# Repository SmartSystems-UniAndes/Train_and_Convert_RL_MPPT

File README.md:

# Train_RL_MPPT
This repository was created for training reinforcement learning agents applied to the problem of maximum power point tracking. It includes the procedure used in order to convert the model to a tensorflowlite agent.  It also includes the schematics of the Buck Converter used to carry out the training process.

To continue deploying the model into the raspberry pi, the next step would be to follow the steps presented in the Github repository presented [here](https://github.com/SmartSystems-UniAndes/Reinforcement_Learning_MPPT_RaspberryPi_Deploy).

## Train_Agent Folder

The Train_Agent folder contains matlab and simulink files that are meant to be used with Matlab2022b. EnvDQN.mlx is a file in which the training parameters are set and the training process can be carried out there. SIM300kW_3paneles.slx is a simulink file that contains the environment used to train the RL model. VariablesBuck_paneles.mlx is a file that contains values for the capacitances and inductances used in the environment. It needs to be run before training the agent and it is excecuted at EnvDQN.mlx. localResetFcn_3paneles.m is a matlab file that resets the environment for each new episode generated. createDQNNetworks.m is the file in which the neural network used to train the DQN agent can be modified. At last, PandOAlgorithm.slx is a file that contains an environment where the Perturb and Observe algorithm can be tested.

## Convert_Agent_To_TFlite Folder
The Convert_Agent_To_TFlite folder contains a matlab script, called convert_script_onnx.m, that converts the agent created into a onnx file. The convert_onnx_to_tflite.ipynb file is intended to be used in google colab. This file allows the user to convert their onnx file to the tensorflow lite framework. The policy.onnx file created must be uploaded to colab to create the tflite model which can be downloaded once created.

## EAGLE_PCB_FILES/Buck300W_with_diode Folder
This folder contains the schematic and layout used to create the 300W synchronous Buck converter to test the models created in real experimental scenarios. It is possible to make it a synchronous  or non-synchronous if a MOSFET or a Diode is added to the low side of the converter. ADD JUST ONE OF THE TWO AT THE LOW SIDE, THE DIODE OR THE MOSFET. If you are using a raspberry pi with this circuit, DO NOT SUPPLY the SD pin of the IR2104 Driver (pin 3) with the 5V of the raspberry PI, this led to undesearable operations in our experiments. Furthermore, remember to add a heat sink to the high power MOSFETs. A diagram that depicts some of the elements of the synchronous buck converter in an schematic format can be seen next:

## Licenses
| Type | License |
| :------: | --- |
| Software    | [MIT License](https://opensource.org/licenses/MIT)     |
| Hardware  | [CERN-OHL-P](https://ohwr.org/project/cernohl/wikis/Documents/CERN-OHL-version-2)        |
| Documentation  | [CC BY 4.0](https://creativecommons.org/licenses/by/4.0/)    |

### Software
The software is licensed under an [MIT License](https://opensource.org/licenses/MIT). A copy of the license has been included in the repository and can be found [here](https://github.com/jfgf11/Reinforcement_Learning_MPPT/blob/main/LICENSE-MIT.txt).

### Hardware
The hardware design files are licensed under a CERN Open Source Hardware license version 2 CERN-OHL-P. Details of the license can be found [here](https://ohwr.org/project/cernohl/wikis/Documents/CERN-OHL-version-2) and a copy of the license has been included [here](https://github.com/jfgf11/Reinforcement_Learning_MPPT_RaspberryPi_Deploy/blob/main/LICENSE-CERN-OHL-P.txt).

### Documentation

This work is licensed under a [Creative Commons Attribution 4.0 International License](https://creativecommons.org/licenses/by/4.0/).

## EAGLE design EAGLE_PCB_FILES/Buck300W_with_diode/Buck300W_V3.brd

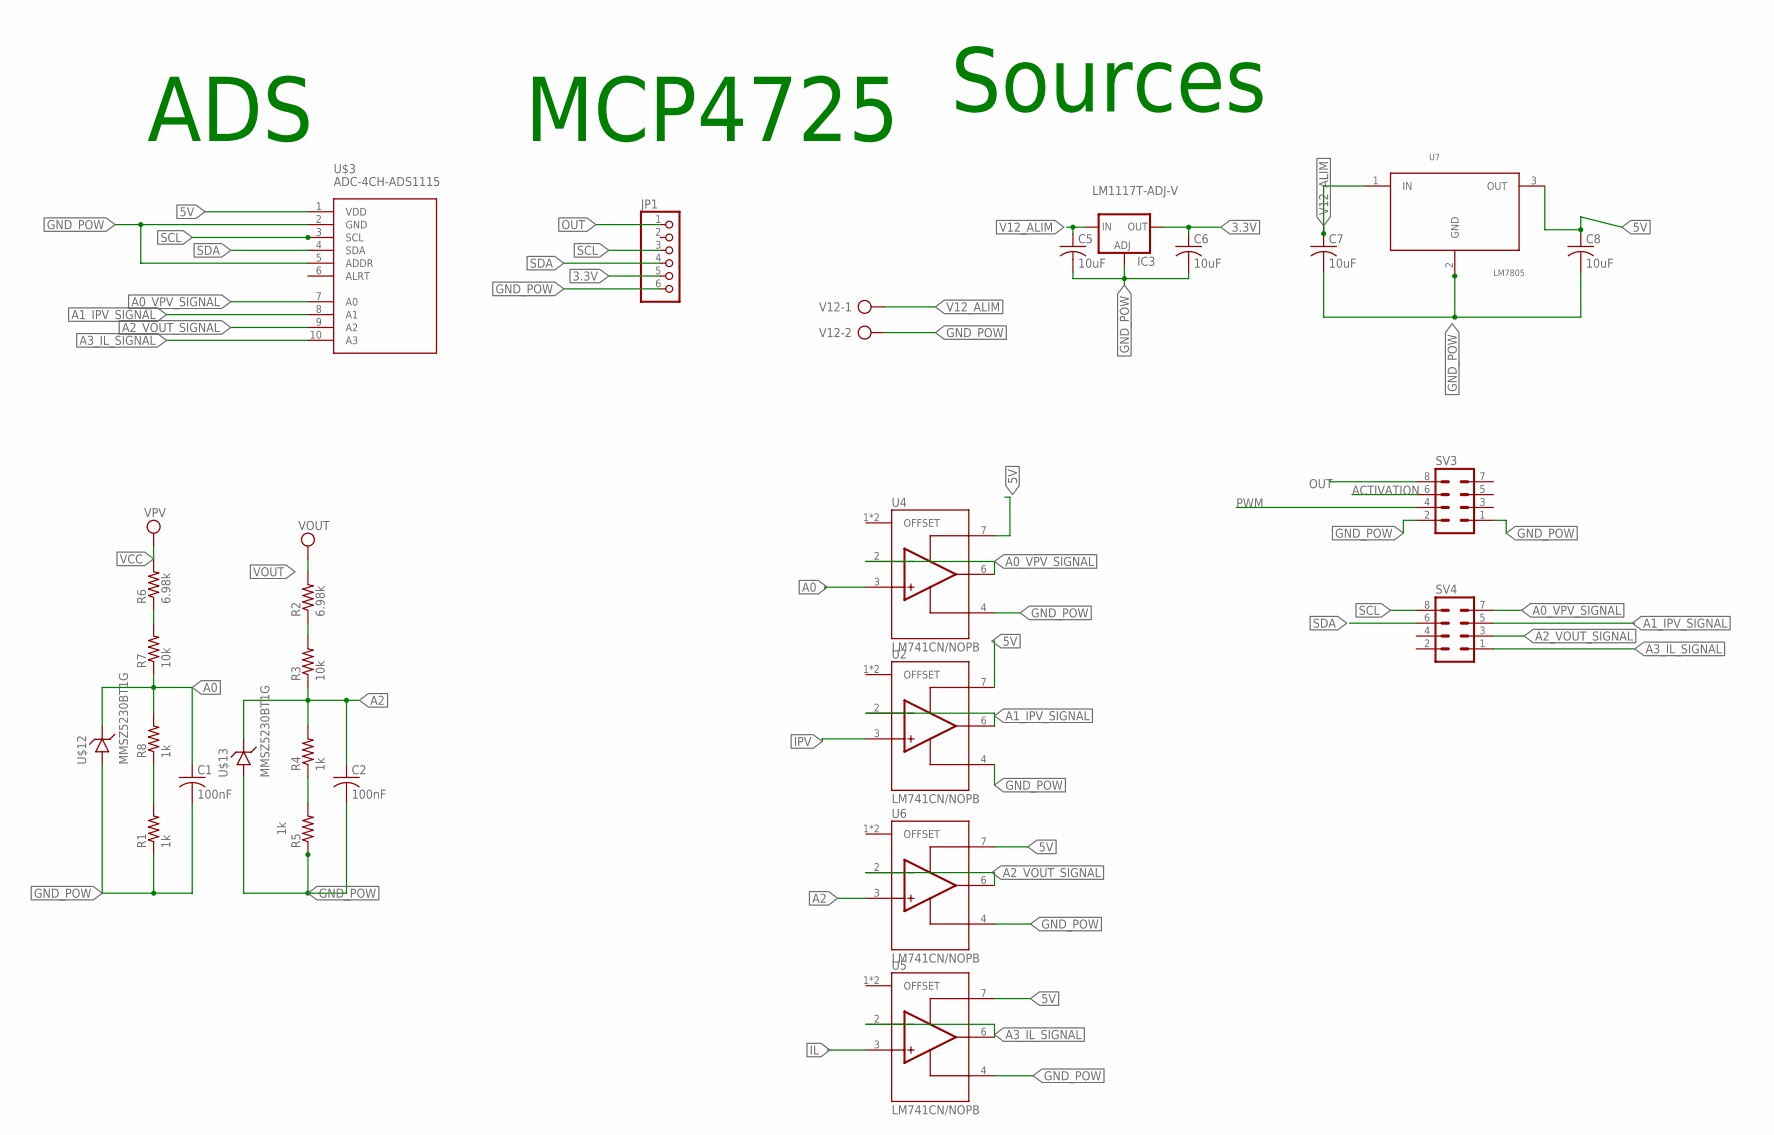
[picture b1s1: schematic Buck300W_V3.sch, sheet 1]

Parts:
C1, C2: 100nF; C0805
C5, C6, C7, C8: 10uF; C025-024X044
IC3: LM1117T-ADJ-V; TO220V
JP1: MICROBUILDER_HEADER-1X6; MICROBUILDER_1X06_OVAL
R1, R4, R5, R8: 1k; R0805
R2, R6: 6.98k; R0805
R3, R7: 10k; R0805
SV3, SV4: MA04-2
U2, U4, U5, U6: LM741CN/NOPB; DIP794W45P254L1016H508Q8
U7: LM7805; TO220
U$3: ADC-4CH-ADS1115
U$12, U$13: MMSZ5230BT1G; SOD3716X135N
V12: AK300/2

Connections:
3.3V: C6.1, IC3.2 (OUT), JP1.5
5V: C8.1, U2.7 (V+), U4.7 (V+), U5.7 (V+), U6.7 (V+), U7.3 (OUT), U$3.1 (VDD); also elsewhere on the board
A0: C1.1, R7.1, R8.2, U4.3 (NON-INV_INPUT), U$12.2 (ANODE)
A0_VPV_SIGNAL: SV4.7, U4.2 (INV_INPUT), U4.6 (OUTPUT), U$3.7 (A0)
A1_IPV_SIGNAL: SV4.5, U2.2 (INV_INPUT), U2.6 (OUTPUT), U$3.8 (A1)
A2: C2.1, R3.1, R4.2, U6.3 (NON-INV_INPUT), U$13.2 (ANODE)
A2_VOUT_SIGNAL: SV4.3, U6.2 (INV_INPUT), U6.6 (OUTPUT), U$3.9 (A2)
A3_IL_SIGNAL: SV4.1, U5.2 (INV_INPUT), U5.6 (OUTPUT), U$3.10 (A3)
ACTIVATION: SV3.6; also elsewhere on the board
GND_POW: C1.2, C2.2, C5.2, C6.2, C7.2, C8.2, IC3.1 (ADJ), JP1.6, R1.1, R5.1, SV3.1, SV3.2, U2.4 (V-), U4.4 (V-), U5.4 (V-), U6.4 (V-), U7.2 (GND), U$3.2 (GND), U$3.5 (ADDR), U$12.1 (CATHODE), U$13.1 (CATHODE), V12.2; also elsewhere on the board
IL: U5.3 (NON-INV_INPUT); also elsewhere on the board
IPV: U2.3 (NON-INV_INPUT); also elsewhere on the board
unnamed: R6.1, R7.2
unnamed: R2.1, R3.2
unnamed: R1.2, R8.1
unnamed: R4.1, R5.2
OUT: JP1.1, SV3.8; also elsewhere on the board
PWM: SV3.4; also elsewhere on the board
SCL: JP1.3, SV4.8, U$3.3 (SCL)
SDA: JP1.4, SV4.6, U$3.4 (SDA)
V12_ALIM: C5.1, C7.1, IC3.3 (IN), U7.1 (IN), V12.1; also elsewhere on the board
VCC: R6.2; also elsewhere on the board
VOUT: R2.2; also elsewhere on the board

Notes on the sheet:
Sources
MCP4725
ADS

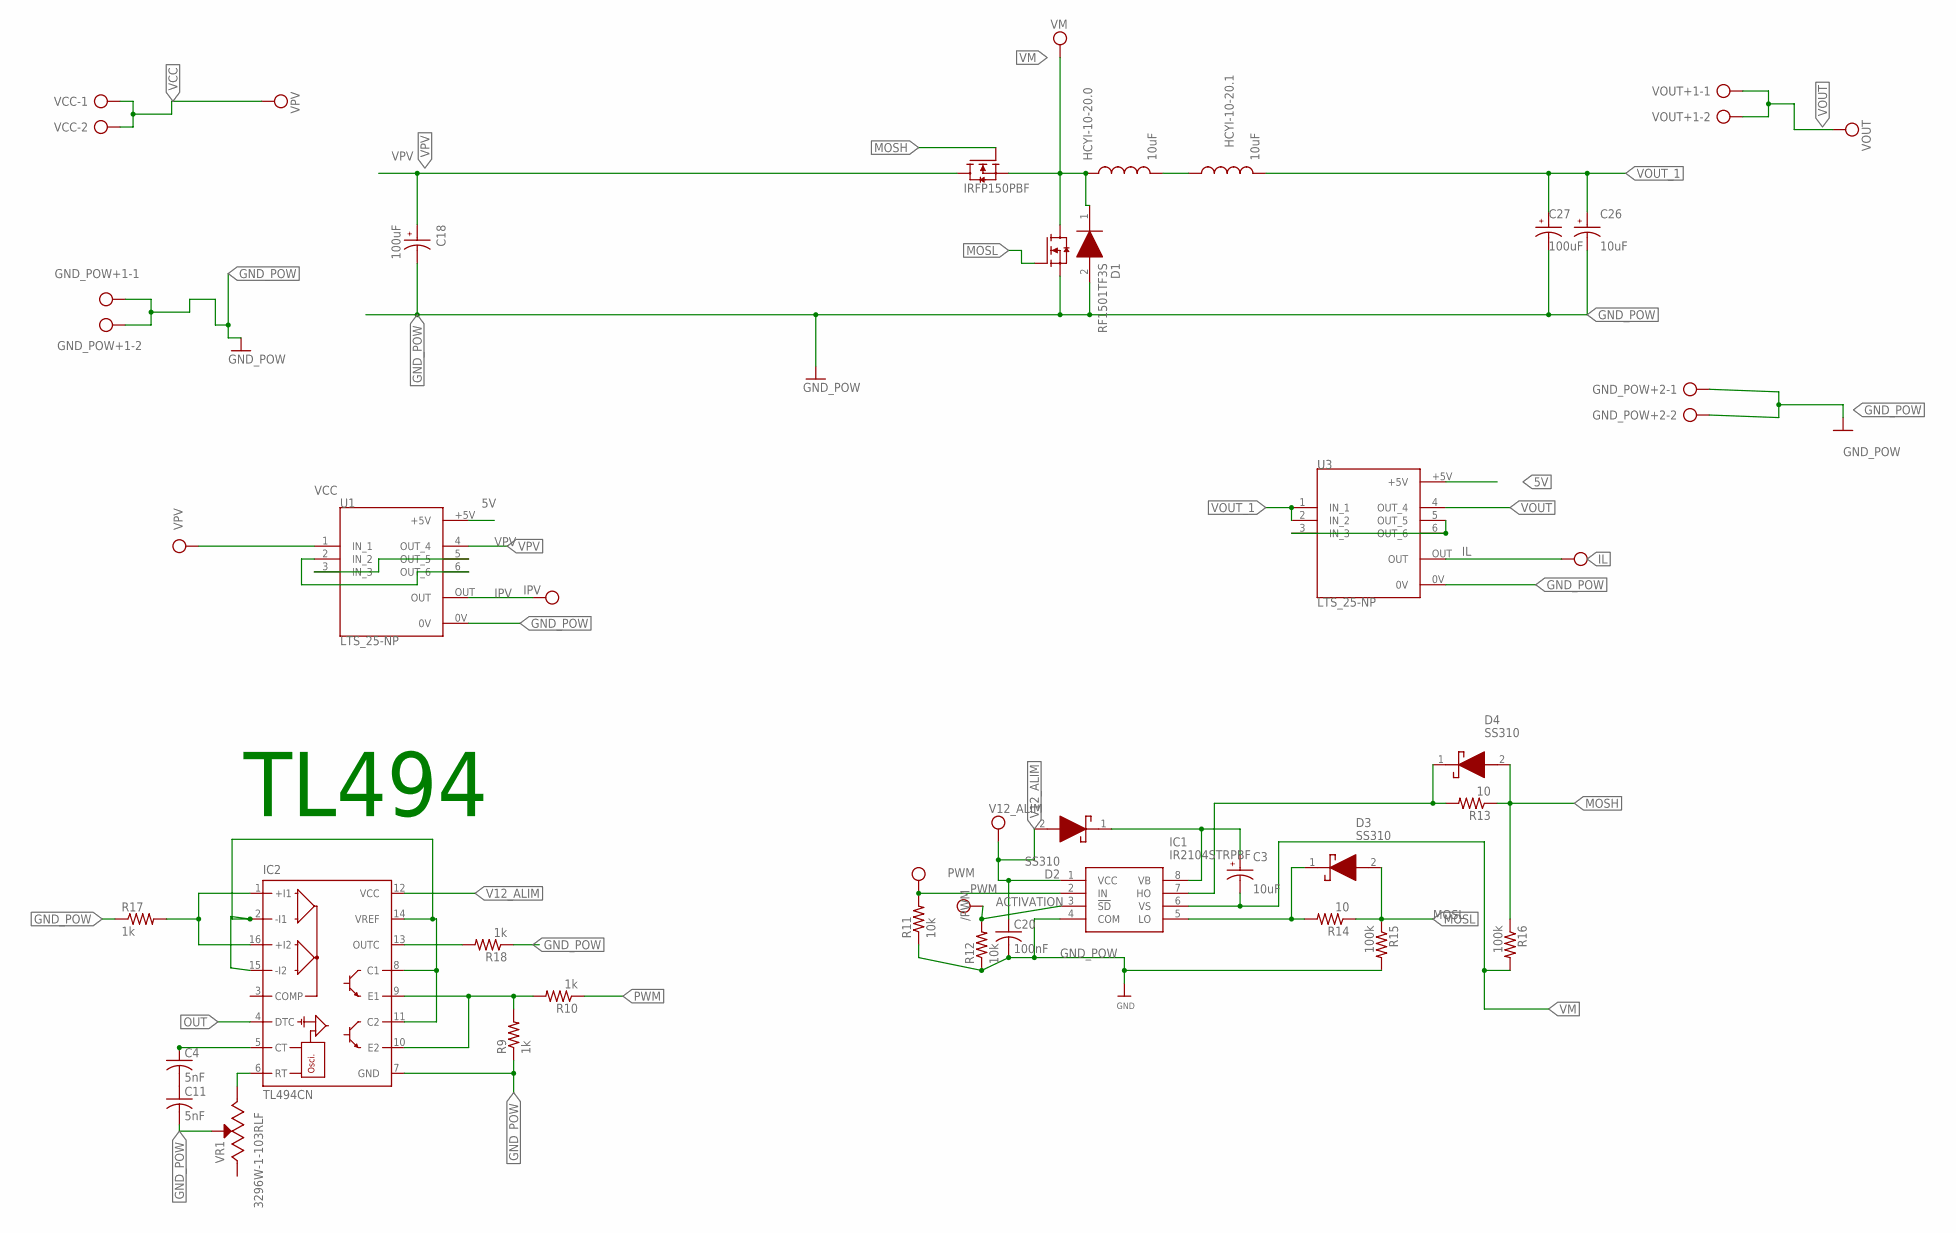
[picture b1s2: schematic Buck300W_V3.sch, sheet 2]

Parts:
C3, C26: 10uF; CAP_EEEFK1J101L
C4, C11: 5nF; C025-024X044
C18, C27: 100uF; CAP_EEEFK1J101L
C20: 100nF; C0805
D1: RF1501TF3S; TO508P450X1010X1840-2P
D2, D3, D4: SS310; DIOM7959X262N
GND_POW+1, GND_POW+2: AK300/2
HCYI-10-20.0, HCYI-10-20.1: 10uF; HCTI-10-20-0
IC1: IR2104STRPBF; SOIC127P600X175-8N
IC2: TL494CN; DIL16
R9, R10, R17, R18: 1k; 0204/5
R11, R12: 10k; R0805
R13, R14: 10; R0805
R15, R16: 100k; R0805
U1, U3: LTS_25-NP; XDCR_LTS_25-NP
U$1, U$2: IRFP150PBF; TO545P1590X530X2460-3
VCC: AK300/2
VOUT+1: AK300/2
VR1: 3296W-1-103RLF; TRIM_3296W-1-103RLF

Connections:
5V: U1.+5V, U3.+5V; also elsewhere on the board
ACTIVATION: IC1.3 (!SD), R12.2; also elsewhere on the board
GND_POW: C11.2, C18.2, C20.2, C26.2, C27.2, D1.2 (A), GND_POW+1.1, GND_POW+1.2, GND_POW+2.1, GND_POW+2.2, IC1.4 (COM), IC2.7 (GND), R9.1, R11.1, R12.1, R15.2, R17.1, R18.1, U1.0V, U3.0V, U$2.3 (S), VR1.2 (WIPER); also elsewhere on the board
IL: U3.OUT; also elsewhere on the board
IPV: U1.OUT; also elsewhere on the board
MOSH: D4.2 (A), R13.1, R16.1, U$1.1 (G)
MOSL: D3.2 (A), R14.1, R15.1, U$2.1 (G)
unnamed: C4.2, C11.1
unnamed: IC2.9 (E1), IC2.10 (E2), R9.2, R10.2
unnamed: C4.1, IC2.5 (CT)
unnamed: IC2.6 (RT), VR1.3 (CW)
unnamed: U3.3 (IN_3), U3.5 (OUT_5), U3.6 (OUT_6)
unnamed: HCYI-10-20.0.2, HCYI-10-20.1.1
unnamed: U1.2 (IN_2), U1.6 (OUT_6)
unnamed: U1.3 (IN_3), U1.5 (OUT_5)
unnamed: IC2.1 (+I1), IC2.16 (+I2), R17.2
unnamed: C3.1, D2.1 (K), IC1.8 (VB)
unnamed: IC2.13 (OUTC), R18.2
unnamed: D4.1 (K), IC1.7 (HO), R13.2
unnamed: D3.1 (K), IC1.5 (LO), R14.2
unnamed: IC2.2 (-I1), IC2.8 (C1), IC2.11 (C2), IC2.14 (VREF), IC2.15 (-I2)
OUT: IC2.4 (DTC); also elsewhere on the board
PWM: IC1.2 (IN), R10.1, R11.2; also elsewhere on the board
V12_ALIM: C20.1, D2.2 (A), IC1.1 (VCC), IC2.12 (VCC); also elsewhere on the board
VCC: U1.1 (IN_1), VCC.1, VCC.2; also elsewhere on the board
VM: C3.2, D1.1 (K), HCYI-10-20.0.1, IC1.6 (VS), R16.2, U$1.3 (S), U$2.2 (D)
VOUT: U3.4 (OUT_4), VOUT+1.1, VOUT+1.2; also elsewhere on the board
VOUT_1: C26.1, C27.1, HCYI-10-20.1.2, U3.1 (IN_1), U3.2 (IN_2)
VPV: C18.1, U1.4 (OUT_4), U$1.2 (D)

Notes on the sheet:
TL494

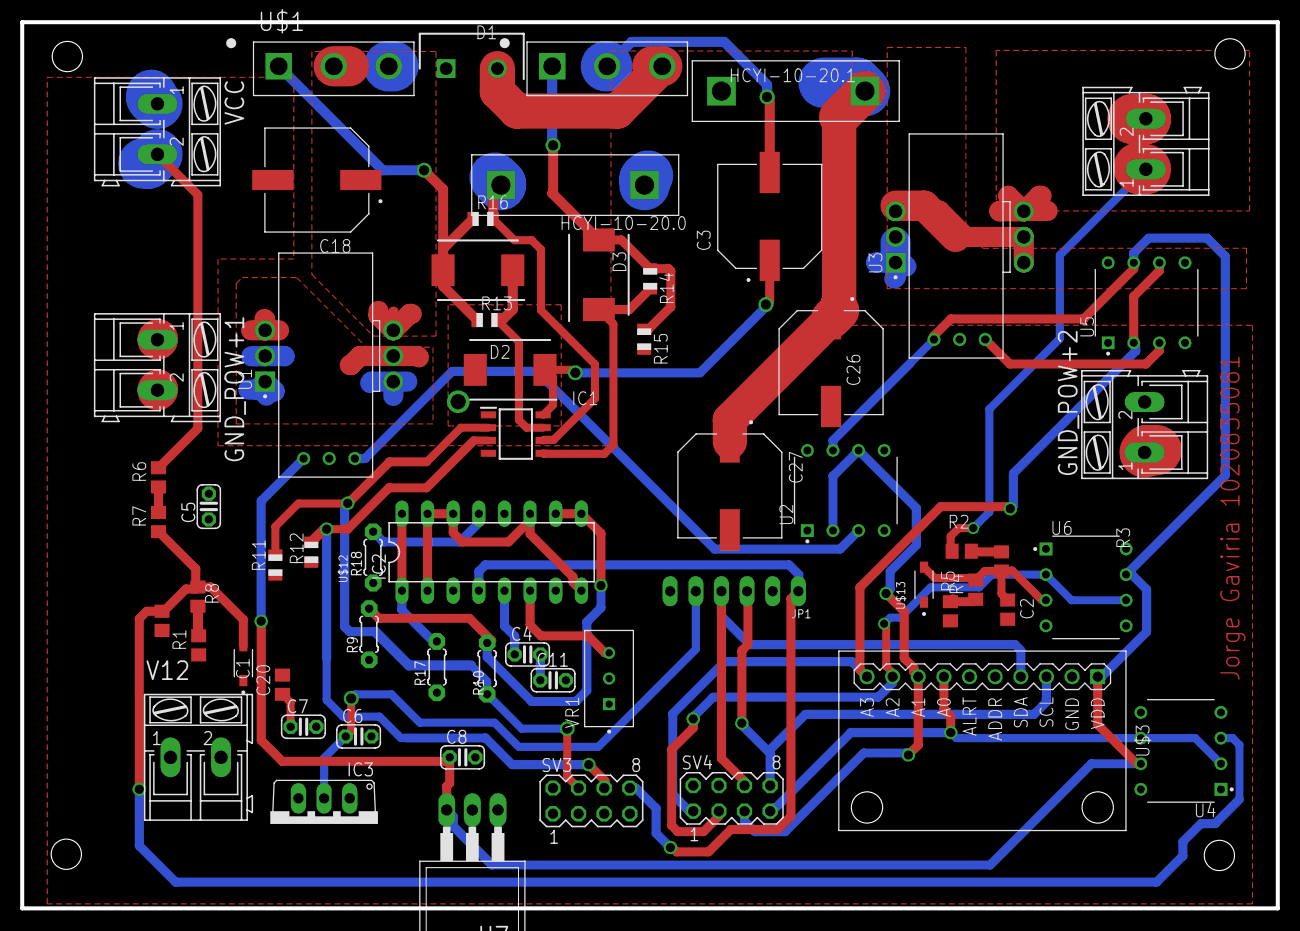
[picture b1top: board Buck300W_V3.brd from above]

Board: 2 copper layers, 124.4 x 87.8 mm, 61 parts (0 on the bottom side), 42 nets.

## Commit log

2022-11-30 Adding training folder, convert folder and eagle files
2022-11-30 explaining each of the folders.
2022-11-30 editing title

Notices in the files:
parts and their libraries:
diy-modules: Released under the Creative Commons Attribution 4.0 International License: http://creativecommons.org/licenses/by/4.0
microbuilder: This work is placed in the public domain, and may be freely used for commercial and non-commercial work with the following conditions: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
